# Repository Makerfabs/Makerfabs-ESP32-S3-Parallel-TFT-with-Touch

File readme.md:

# Makerfabs ESP32-S3 Parallel TFT with Touch

```c++
/*
Version:		V1.3
Author:			Vincent
Create Date:	2022/5/24
Note:
	2022/12/29	V1.3:Change wiki link.
	2022/10/7	V1.2:Add USB HID example.
	2022/10/7	V1.1:Add USB HID example.
*/
```

[toc]

# Makerfabs

[Makerfabs home page](https://www.makerfabs.com/)

[Makerfabs Wiki](https://wiki.makerfabs.com/)

# Makerfabs ESP32-S3 Parallel TFT with Touch
## Intruduce

Product Link ：[ESP32-S3 Parallel TFT with Touch 3.5'' ILI9488](https://www.makerfabs.com/esp32-s3-parallel-tft-with-touch-ili9488.html)

Wiki Link : [ESP32-S3 Parallel 3.5'' TFT with Touch](https://wiki.makerfabs.com/ESP32_S3_Parallel_3.5_TFT_with_Touch.html)

The 3.5" 320x480 TFT LCD driver is ILI9488, it uses 16bits parallel line for communication with ESP32-S3, the main clock could be up to 20MHz, make the display smooth enough for videos; You can freely use some of Mabee pins(A I2c and a IOs) with the breakout connectors, to connect the ESP32-S3 display with sensors/ actuators, suitable for IoT applications.

## Feature

- Wi-Fi (2.4 GHz band)
- Bluetooth Low Energy
- Dual high performance Xtensa® 32-bit LX7 CPU cores
- Ultra Low Power co-processor running either RISC-V or FSM core
- Multiple peripherals
- Built-in security hardware
- USB OTG interface
- USB Serial/JTAG Controller
- Arduino Compatible: You can play it with Arduino IDE
- LCD 3.5 inch Amorphous-TFT-LCD (Thin Film Transistor Liquid Crystal Display) for mobile-phone or handy electrical equipment
- LCD Driver: ILI9488(16bits parallel line)
- LCD Resolution: 320*480
- FT6236 Series ICs are single-chip capacitive touch panel controller IC with a built-in 16 bit enhanced Micro-controller unit (MCU)
- NS2009: A 4-wire resistive touch screen control circuit with I2C interface, which contains A 12-bit resolution A/D converter
- Power supply: 5V, Type-C USB
- Micro SD card slot on the board
- Dual USB Type-C: one for native USB and one for USB-to-UART
- Two Mabee interfaces
- Board size: 66mm * 85mm

# Code Explain

## Complier Option

- Install board : ESP32 .
- Install library : LovyanGFX library. 
- Edit the code based on the touch screen. If you use resistive screen, choice NS2009_TOUCH. If you use capacitive screen, choice FT6236_TOUCH. 
- Use type-c use cable connect USB-TTL to PC.
- Upload codes, select "ESP32-S3 DEV Module" and "UART0"

## Firmware

### SD16_3.5

Factory firmware. First run the boot self-test to check the hardware. Press down the middle of the touch screen as prompted to display a LOGO picture on the SD card. Finally, print the touch coordinates in the serial port.

## Example

### touch_keyboard

The ESP32S3 native USB is used, which can be used as a USB HID to simulate a keyboard.

You can input text, key combination, enter key, and connect to the NTP server through WiFi, output real-time time.

### touch_keyboard V2.0

Added an inherited three custom keyboard keyboard Demo, including text input + key combination, numeric keypad, arrow keys + space.

### PDQgraphicstest

Arduino GFX Library display demo.

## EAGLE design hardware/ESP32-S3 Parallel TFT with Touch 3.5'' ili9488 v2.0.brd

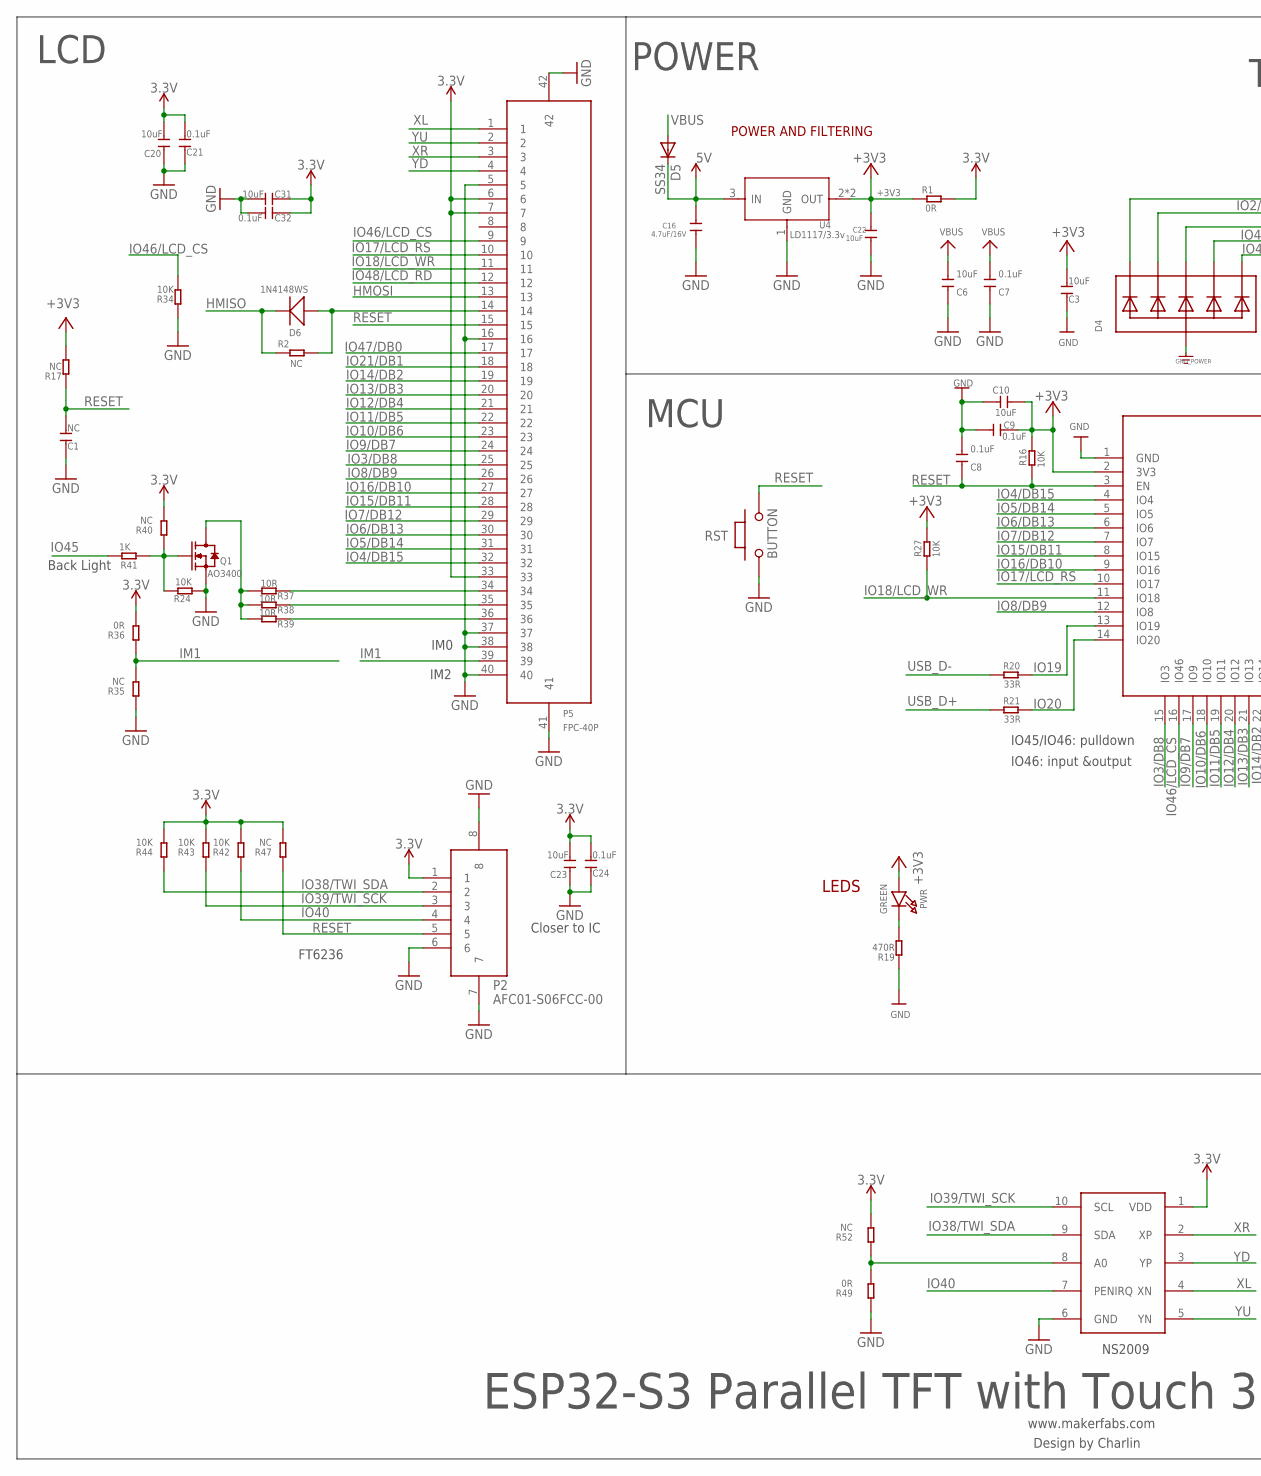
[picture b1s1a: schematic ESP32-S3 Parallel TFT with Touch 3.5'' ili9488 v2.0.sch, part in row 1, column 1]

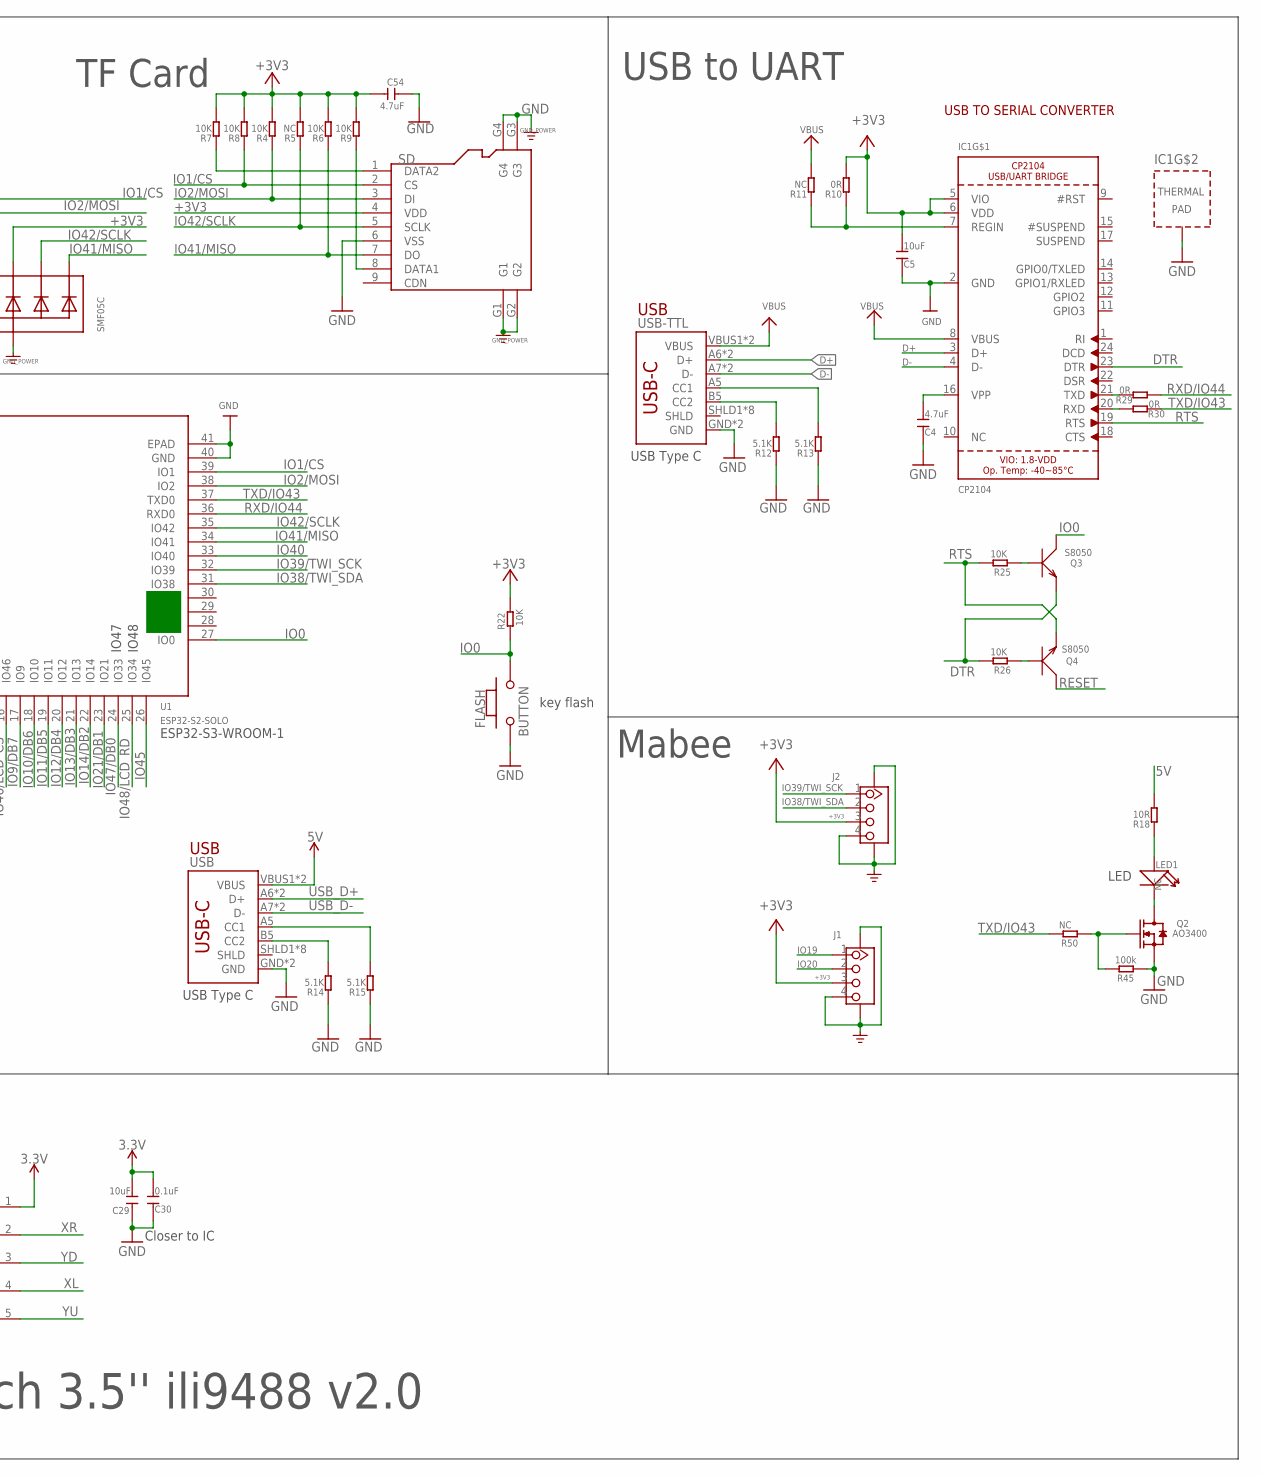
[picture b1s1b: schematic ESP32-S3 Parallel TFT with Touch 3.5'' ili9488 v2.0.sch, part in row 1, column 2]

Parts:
C1: NC; DISCRETE_C0603
C3, C5, C6, C10, C20, C23, C29, C31: 10uF; DISCRETE_C0603
C4, C54: 4.7uF; DISCRETE_C0603
C7, C8, C9, C21, C24, C30, C32: 0.1uF; DISCRETE_C0603
C16: 4.7uF/16V; 0603
C22: 10uF; 0603
D4: SMF05C; SOT363
D5: SS34; DO-214AC
D6: 1N4148WS; SOD323
FLASH: BUTTON; 157SW
IC1: CP2104; QFN24_4MM_SMSC
J1, J2: GROVE-CONNECTOR-SMD'90D'; HW4-SMD-2.0-90D
LED1: NC; DISCRETE_LED-3528
P2: AFC01-S06FCC-00; SMD8-50P-740L535W
P5: FPC-40P; SMD42-50P-2560L490W
PWR: GREEN; CHIPLED_0805_NOOUTLINE
Q1, Q2: AO3400; SOT23@1
Q3, Q4: S8050; SOT23
R1, R29, R30: 0R; R0603
R2, R50: NC; R0603
R4, R6, R7, R8, R9, R24, R34, R42, R43, R44: 10K; DISCRETE_R0603
R5, R11, R17, R35, R40, R47, R52: NC; DISCRETE_R0603
R10, R36, R49: 0R; DISCRETE_R0603
R12, R13, R14, R15: 5.1K; DISCRETE_R0603
R16, R22, R25, R26, R27: 10K; R0603
R18, R37, R38, R39: 10R; DISCRETE_R0603
R19: 470R; DISCRETE_R0603
R20, R21: 33R; R0603
R41: 1K; DISCRETE_R0603
R45: 100k; R0603
RST: BUTTON; 157SW
SD: HOLDER-MICROSD-9P; 9P-SMD-W/-RING
U1: ESP32­S2­SOLO; ESP32-­S2-­SOLO
U4: LD1117/3.3v; SOT89
U8: NS2009; MSOP10
USB: USB_C5; USB-C-16P-5
USB-TTL: USB_C5; USB-C-16P-5

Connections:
3.3V: C20.2, C21.2, C23.2, C24.2, C29.2, C30.2, C31.1, C32.1, P2.1, P5.6, P5.7, P5.33, R1.2, R36.2, R40.2, R42.2, R43.2, R44.2, R47.2, R52.2, U8.1 (VDD)
5V: C16.1, D5.C, R18.2, U4.3 (IN), USB.VBUS1 (VBUS), USB.VBUS2 (VBUS)
+3V3: C3.2, C5.2, C9.1, C10.1, C22.1, C54.2, D4.4 (C3), IC1.5 (VIO), IC1.6 (VDD), J1.3, J2.3, PWR.A, R1.1, R4.2, R5.2, R6.2, R7.2, R8.2, R9.2, R10.2, R16.2, R17.2, R22.2, R27.2, SD.4 (VDD), U1.2 (3V3), U4.2 (OUT), U4.4 (OUT)
D+: IC1.3 (D+), USB-TTL.A6 (D+), USB-TTL.B6 (D+)
D-: IC1.4 (D-), USB-TTL.A7 (D-), USB-TTL.B7 (D-)
DTR: IC1.23 (DTR), Q3.2 (E), R26.2
GND: C1.1, C3.1, C4.1, C5.1, C6.1, C7.1, C8.2, C9.2, C10.2, C16.2, C20.1, C21.1, C22.2, C23.1, C24.1, C29.1, C30.1, C31.2, C32.2, C54.1, D4.2 (A), FLASH.1, IC1.2 (GND), IC1.THERM (TP), J1.4, J1.SS1, J1.SS2, J2.4, J2.SS1, J2.SS2, P2.6, P2.7, P2.8, P5.5, P5.16, P5.37, P5.38, P5.40, P5.41, P5.42, Q1.2 (S), Q2.2 (S), R12.1, R13.1, R14.1, R15.1, R19.1, R24.1, R34.1, R35.1, R45.1, R49.1, RST.1, SD.6 (VSS), SD.G1, SD.G2, SD.G3, SD.G4, U1.1 (GND), U1.40 (GND), U1.41 (EPAD), U4.1 (GND), U8.6 (GND), USB.GND, USB.GND2 (GND), USB-TTL.GND, USB-TTL.GND2 (GND)
HMISO: D6.-, R2.1
HMOSI: P5.13
IM1: P5.39, R35.2, R36.1
IO0: FLASH.2, Q3.3 (C), R22.1, U1.27 (IO0)
IO1/CS: D4.1 (C1), R8.1, SD.2 (CS), U1.39 (IO1)
IO2/MOSI: D4.3 (C2), R4.1, SD.3 (DI), U1.38 (IO2)
IO3/DB8: P5.25, U1.15 (IO3)
IO4/DB15: P5.32, U1.4 (IO4)
IO5/DB14: P5.31, U1.5 (IO5)
IO6/DB13: P5.30, U1.6 (IO6)
IO7/DB12: P5.29, U1.7 (IO7)
IO8/DB9: P5.26, U1.12 (IO8)
IO9/DB7: P5.24, U1.17 (IO9)
IO10/DB6: P5.23, U1.18 (IO10)
IO11/DB5: P5.22, U1.19 (IO11)
IO12/DB4: P5.21, U1.20 (IO12)
IO13/DB3: P5.20, U1.21 (IO13)
IO14/DB2: P5.19, U1.22 (IO14)
IO15/DB11: P5.28, U1.8 (IO15)
IO16/DB10: P5.27, U1.9 (IO16)
IO17/LCD_RS: P5.10, U1.10 (IO17)
IO18/LCD_WR: P5.11, R27.1, U1.11 (IO18)
IO19: J1.1, R20.2, U1.13 (IO19)
IO20: J1.2, R21.2, U1.14 (IO20)
IO21/DB1: P5.18, U1.23 (IO21)
IO38/TWI_SDA: J2.2, P2.2, R44.1, U1.31 (IO38), U8.9 (SDA)
IO39/TWI_SCK: J2.1, P2.3, R43.1, U1.32 (IO39), U8.10 (SCL)
IO40: P2.4, R42.1, U1.33 (IO40), U8.7 (PENIRQ)
IO41/MISO: D4.6 (C5), R6.1, SD.7 (DO), U1.34 (IO41)
IO42/SCLK: D4.5 (C4), R5.1, SD.5 (SCLK), U1.35 (IO42)
IO45: R41.2, U1.26 (IO45)
IO46/LCD_CS: P5.9, R34.2, U1.16 (IO46)
IO47/DB0: P5.17, U1.24 (IO33)
IO48/LCD_RD: P5.12, U1.25 (IO34)
unnamed: C4.2, IC1.16 (VPP)
unnamed: Q4.1 (B), R26.1
unnamed: Q3.1 (B), R25.1
unnamed: D6.+, P5.14, R2.2
unnamed: Q2.1 (G), R45.2, R50.1
unnamed: R15.2, USB.A5 (CC1)
unnamed: PWR.C, R19.2
unnamed: LED1.1 (+), R18.1
unnamed: LED1.2 (-), Q2.3 (D)
unnamed: R13.2, USB-TTL.A5 (CC1)
unnamed: R12.2, USB-TTL.B5 (CC2)
unnamed: IC1.7 (REGIN), R10.1, R11.1
unnamed: R14.2, USB.B5 (CC2)
unnamed: IC1.21 (TXD), R29.2
unnamed: IC1.20 (RXD), R30.2
unnamed: P5.34, R37.1
unnamed: P5.35, R38.1
unnamed: P5.36, R39.1
unnamed: Q1.1 (G), R24.2, R40.1, R41.1
unnamed: Q1.3 (D), R37.2, R38.2, R39.2
unnamed: R49.2, R52.1, U8.8 (A0)
unnamed: R7.1, SD.1 (DATA2)
unnamed: R9.1, SD.8 (DATA1)
RESET: C1.2, C8.1, P2.5, P5.15, Q4.3 (C), R16.1, R17.1, R47.1, RST.2, U1.3 (EN)
RTS: IC1.19 (RTS), Q4.2 (E), R25.2
RXD/IO44: R29.1, U1.36 (RXD0)
TXD/IO43: R30.1, R50.2, U1.37 (TXD0)
USB_D+: R21.1, USB.A6 (D+), USB.B6 (D+)
USB_D-: R20.1, USB.A7 (D-), USB.B7 (D-)
VBUS: C6.2, C7.2, D5.A, IC1.8 (VBUS), R11.2, USB-TTL.VBUS1 (VBUS), USB-TTL.VBUS2 (VBUS)
XL: P5.1, U8.4 (XN)
XR: P5.3, U8.2 (XP)
YD: P5.4, U8.3 (YP)
YU: P5.2, U8.5 (YN)

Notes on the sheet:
www.makerfabs.com
Design by Charlin
USB
LEDS
POWER AND FILTERING
USB TO SERIAL CONVERTER
key flash
ESP32-S3 Parallel TFT with Touch 3.5'' ili9488 v2.0
POWER
USB to UART
USB Type C
TF Card
LED
NS2009
FT6236
Closer to IC
Back Light
IM0
IM2
IO45/IO46: pulldown
IO46: input &output
Mabee
LCD
MCU
ESP32-S3-WROOM-1
IO47
IO48

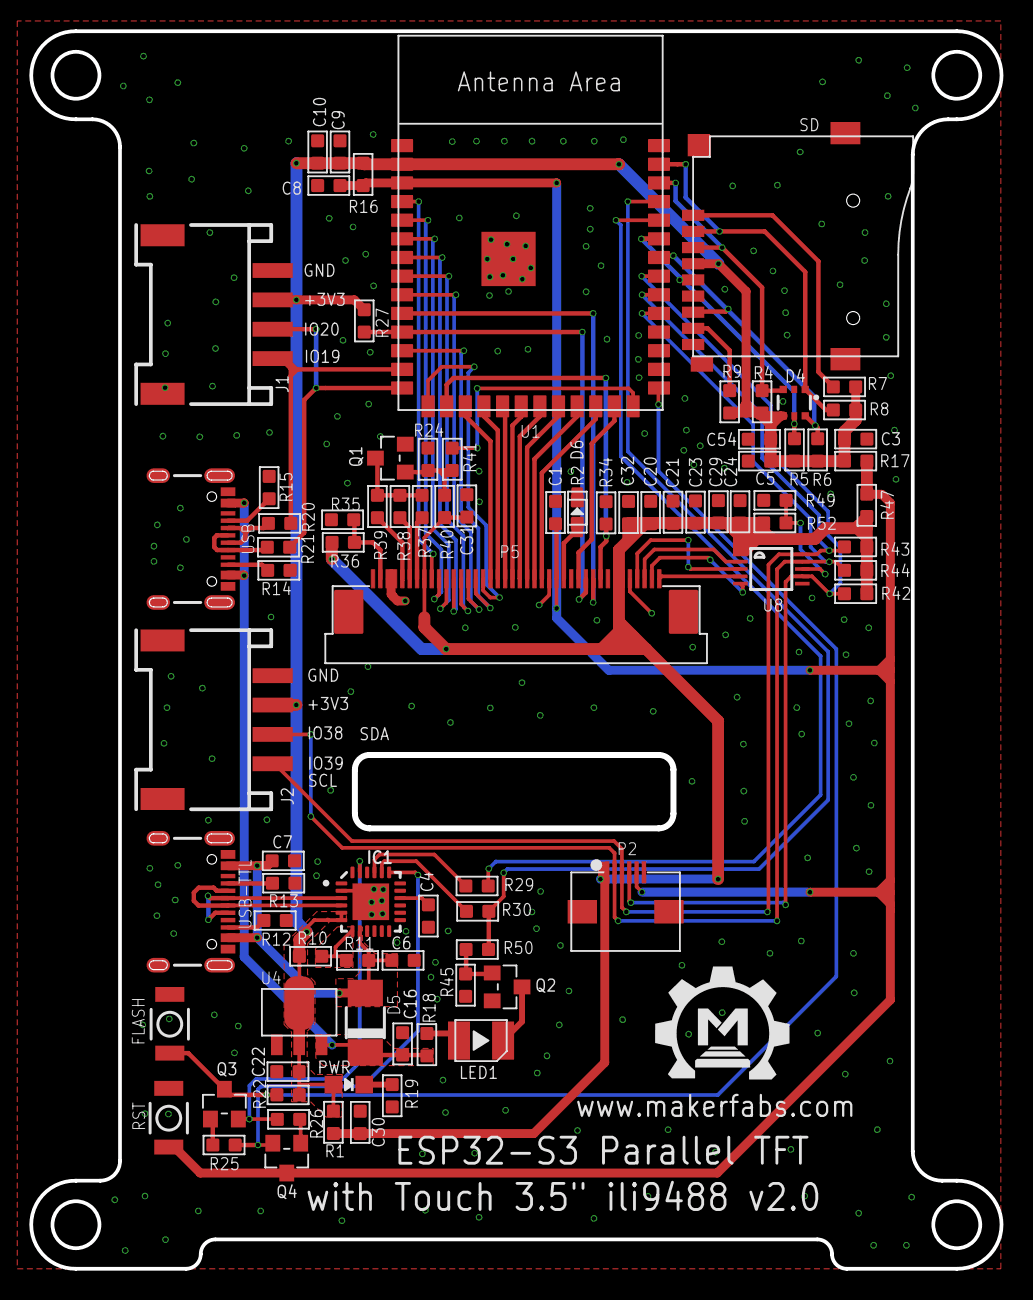
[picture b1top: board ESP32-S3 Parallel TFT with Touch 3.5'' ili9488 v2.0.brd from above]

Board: 2 copper layers, 65.9 x 84.1 mm, 86 parts (0 on the bottom side), 74 nets.

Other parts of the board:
U$1: MAKERFABS_0.3

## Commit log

2022-05-24 Create project
2022-06-29 Add hardware
2022-07-01 Improved perf of logo display
2022-10-07 Add USB HID demo
2022-10-09 TouchKeyboardV2.0
2023-03-09 Add tvoc demo
2024-07-12 add new version
2024-07-12 Revert "Delete old version file."
    This reverts commit ae68940200865531560fb4ac1a0bfb5abab0bc47.
2024-09-23 add PlatformIO demo
2024-09-24 add demo
2024-12-16 Add youtube project
2025-03-25 Add Arduino GFX Library display demo
2025-06-13 Add Youtube video code
2025-11-20 add esp-idf examples
2025-11-20 rm .vscode
2026-01-04 update idf example

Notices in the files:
parts and their libraries:
microbuilder: This work is placed in the public domain, and may be freely used for commercial and non-commercial work with the following conditions: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
SparkFun-PowerSymbols: Licensing: Creative Commons ShareAlike 4.0 International - https://creativecommons.org/licenses/by-sa/4.0
